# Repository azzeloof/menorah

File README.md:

# menorah
A PCB menorah!
This is a work in progress, though I've ordered boards so I hope the hardware is correct. The majority of the circuit is copied from [the snowflake ornament I worked on last year](https://github.com/azzeloof/snowflake), but some parts of this circuit (the pinout of the programming header) are untested.

PCB aside, the total component cost comes to less than $10. You'll need an AVR programmer too (though I think you can use an Arduino).

Firmware will be added soon. I wanted to post this as soon as I finished the hardware in case anybody wants to make one in time for Hanukkah!

# hardware
*BOM Change* I made a mistake in the board layout. For the ATTiny85, I used the same footprint I used on the snowflake, which is a SMD footprint for a DIP-8 socket. I should have used a SOIC-8 footprint to accommodate the SMD ATTiny85 I chose. The BOM has been updated to include a socket and THT ATTiny85. The other (and probably better) approach would be to update the board layout to use the correct footprint.
The board is a sample two-layer PCB. I ordered from PCBWay, because they'll make boards with a blue solder mask and white siklscreen. I used lead-free HASL as a copper finish. Immersion silver might look good too, though it's expensive, it can tarnish, and takes longer to produce. Honestly I woulda probably gone with it if lead time wasn't an issue.
ENIG or hard gold would look good too if you'd rather go for that look.

If you want to make your own, you can take the gerbers from the hardware directory.
It can be [directly ordered from PCBWay](https://www.pcbway.com/project/shareproject/LED_Menorah.html) also.

Controller is an ATtiny85, and power comes from a AAA battery pack that gets adhered to the back (it also acts as a support). LEDs are reverse-mounted to shine through the board. Resistor values in the schematic are set for blue LEDs, but I'll probably change them to red or yellow. Use whichever colors you'd like, just make sure to set the resistors appropriatley. 

# firmware
coming soon

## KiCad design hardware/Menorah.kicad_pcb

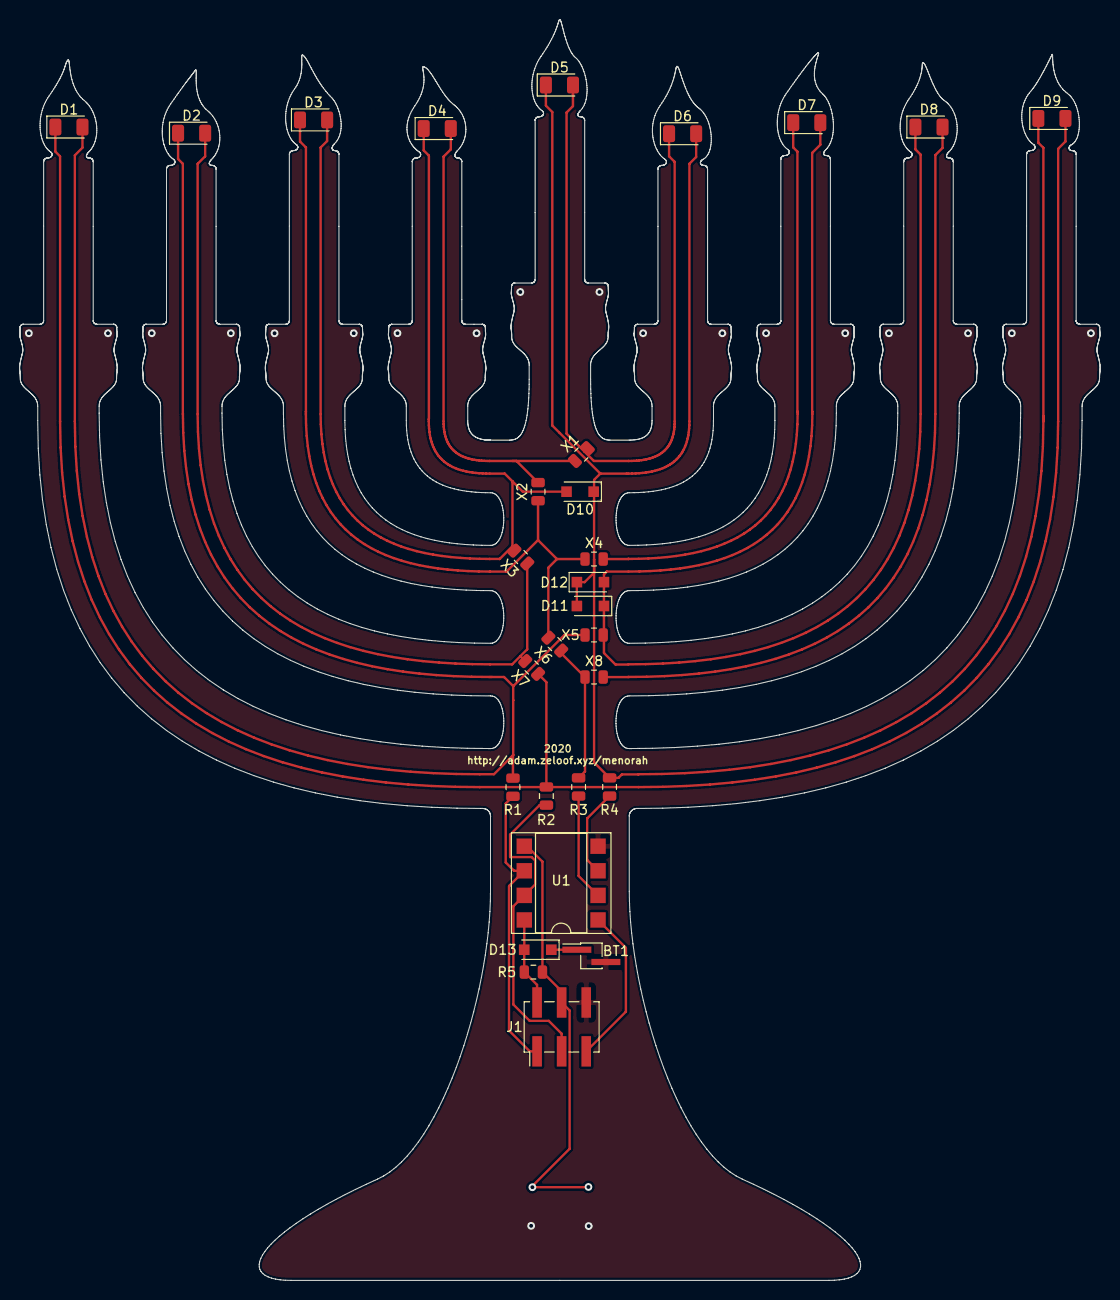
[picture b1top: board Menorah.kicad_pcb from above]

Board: 2 copper layers, 111.6 x 130.3 mm, 30 parts (1 on the bottom side), 13 nets.

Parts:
BT1: Battery; PinHeader_1x02_P1.27mm_Vertical_SMD_Pin1Left
D1, D2, D3, D4, D5, D6, D7, D8, D9: LED; LED_1206_3216Metric
D10, D11, D12, D13: 1N4004; D_SOD-123F
J1: Conn_02x03_Odd_Even; PinHeader_2x03_P2.54mm_Vertical_SMD
R1, R2, R3, R4: 68; R_0805_2012Metric
R5: 4k7; R_0805_2012Metric
SW1: SW_Push; SW_Push_1P1T_NO_CK_KSC6xxJ
U1: ATtiny85-20PU; DIP-8_W7.62mm_SMDSocket_SmallPads
X1, X2, X3, X4, X5, X6, X7, X8: R_0805_2012Metric

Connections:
GND: BT1.2, J1.6, SW1.2, U1.4
MISO: J1.1, R1.2, U1.6
MOSI: J1.4, R5.1, SW1.1, U1.5
unnamed: BT1.1, D13.1
unnamed: D1.1, D2.2, D3.2, D4.1, D9.2, D10.2, R2.1, X3.1, X3.2, X7.1, X7.2
unnamed: D1.2, D2.1, D7.2, D8.1, D11.1, D12.2, R1.1, X5.1, X5.2
unnamed: D3.1, D4.2, D5.2, D6.1, D7.1, D8.2, R3.1, X1.1, X1.2, X2.1, X2.2, X4.1, X4.2, X6.1, X6.2, X8.1, X8.2
unnamed: D5.1, D6.2, D9.1, D10.1, D11.2, D12.1, R4.1
unnamed: R3.2, U1.2
unnamed: R4.2, U1.3
RST: J1.5, U1.1
SCK: J1.3, R2.2, U1.7
VCC: D13.2, J1.2, R5.2, U1.8

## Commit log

2020-11-19 Initial PCB artwork
2020-11-19 updated schematic
2020-11-19 assigned footprints, started layout
2020-11-20 placement progress
2020-11-23 lotsa stuff
2020-11-24 layout progress
2020-11-24 fixed ground planes
2020-11-24 Finished (?) layout, ordered boards.
2020-11-24 wrote readme
2020-11-25 Added BOM
2020-12-01 Updated BOM to fix footprint mistake
2020-12-03 added snowflake firmware
2020-12-06 firmware working
2020-12-06 Updated firmware, added changelog
2020-12-06 got rid of delay() function
2021-11-27 PlatformIO config fixes
    Looks like PlatformIO's Attiny85 definition changed and messed up some things. This should fix it.
